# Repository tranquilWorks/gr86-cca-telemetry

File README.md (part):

# CCA Telemetry (GR86 / BRZ Gen2)

## GR86 CCA assurance

The findings-only integration and local Codex prompts are in
[assurance/README.md](assurance/README.md). It binds the current I32 sourced
Rev B package to the shared framework. Fresh native assessment is blocked by
the KiCad 9/10 compatibility gap; software checks do not approve the board.
See [source effectivity](assurance/DISCOVERY.md) before using older descriptions below.

**Current Rev B ECAD and manufacturing:** [sourced I32 handoff](docs/engineering/rvb22/product/PRODUCT_HANDOFF.md).
The native project, BOM, CPL and fabrication files are reconciled; supplier sourcing and physical qualification gates remain open.

CCA Telemetry is a RaceChrono-compatible telemetry stack for the Toyota GR86 / Subaru BRZ (ZN8/ZD8) platform. An ESP32-S3 collects CAN, GPS, and auxiliary analog data, then streams it over Bluetooth Low Energy using RaceChrono's DIY device profile. The codebase is designed for track reliability: aggressive BLE reconnects, TWAI burst handling, persistent configuration, and configurable CAN filtering are all built in.

Hardware bring-up (CAN transceiver wiring, GPS, OLEDs, etc.) is intentionally out of scope here—assume those pieces are already handled. This repository focuses on the firmware, documentation, and validation artifacts you need to build, modify, and deploy the project.

## What this guide covers

* **End-to-end bring-up.** The “Track-day bring-up checklist” walks from flashing through wiring, BLE pairing, and pre-session validation so even a first-time CAN user can connect, configure, and verify the module before heading out.【F:README.md†L46-L125】
* **Subsystem deep dives.** “Firmware architecture,” “Oil pressure channel & calibration,” and the PID-map sections explain how each feature works (CAN ingest, BLE, GPS/PPS, oil analog path, pidmaps) and point directly to the source files for further hacking.【F:README.md†L77-L150】【F:README.md†L206-L213】
* **Runtime operations.** The Serial CLI reference documents every SHOW/PROFILE/ALLOW/FIL/TOKEN/RATE/SAVE command so you can administer the device without reflashing once it is installed in the car.【F:README.md†L214-L244】
* **RaceChrono & filtering workflows.** The RaceChrono integration, `.fil` ingestion walkthrough, and pidmap cloning guide teach you how to curate channels from the phone or at compile time, keeping CAN/BLE bandwidth under control.【F:README.md†L131-L150】【F:README.md†L180-L213】
* **Diagnostics & recovery.** LED pin/pattern tables, the troubleshooting checklist, and persistent-configuration guidance translate firmware counters into hands-on fixes at the car so you can recover from CAN, BLE, GPS, or oil faults mid-event.【F:README.md†L114-L130】【F:README.md†L123-L178】【F:README.md†L238-L244】

Together these sections document the full software feature set—from CAN filtering to RaceChrono streaming and oil calibration—so newcomers can treat the README as a production-ready operations guide.

## Release-ready polish

To make the repo publishable as an open-source reference design, every workflow called out in prior PRs is now paired with actionable guidance in this README:

* **Single source of truth.** The Track-day checklist, subsystem deep dives, CLI catalog, and RaceChrono workflows are all anchored to the implementation files they describe, so readers can jump from prose to code while auditing the feature set.
* **Operator focus.** Each runtime touch point—PID governance, GPS/PPS, oil calibration, RaceChrono filters, persistence—includes both “how it works” and “how to recover” instructions so someone new to CAN can confidently run the module at the track.
* **Debug-to-code breadcrumbs.** LED tables, SHOW/CAL output, and `.fil` logging now cite the handlers that emit those diagnostics, letting contributors trace symptoms back to the firmware without guesswork.

This section is the final assurance that the README stands alone as a production-ready operations manual: new users get the high-level tour at the top, the detailed workflows in the middle, and the debug/persistence references at the end without needing outside docs.

## Feature matrix & documentation coverage

| Feature / decision | Where it lives in code | Where to configure / operate it |
|--------------------|------------------------|----------------------------------|
| CAN burst ingestion, TWAI error recovery, PID throttling | `firmware/cca_telemetry.ino` main loop + TWAI handlers | *Firmware architecture → CAN ingestion & PID governance* and *Track-day bring-up checklist* describe how to wire and validate the bus before driving.【F:firmware/cca_telemetry.ino†L205-L235】【F:README.md†L23-L71】 |
| BLE transport, RaceChrono DIY profile, diagnostics notify | NimBLE setup in `firmware/cca_telemetry.ino` | *Track-day bring-up checklist → Pair with RaceChrono*, *RaceChrono integration*, and the troubleshooting bullets tie the LEDs, CLI, and `.fil` workflow together for new users.【F:firmware/cca_telemetry.ino†L89-L146】【F:README.md†L40-L73】【F:README.md†L120-L152】 |
| GPS + PPS time discipline | `firmware/src/gps_nmea.*`, PPS ISR in the sketch | *Firmware architecture → GPS & PPS discipline* plus the LED/troubleshooting tables walk through wiring, lock states, and debugging steps.【F:firmware/src/gps_nmea.cpp†L1-L210】【F:README.md†L75-L152】 |
| Oil pressure sampling, filtering, calibration, and CAN 0x710 publisher | Analog path in `firmware/cca_telemetry.ino` + `nvs_cfg.*` | *Track-day bring-up checklist*, *Oil pressure channel & calibration*, and the CLI section spell out how to hook up sensors, capture endpoints, and stream the data.【F:firmware/cca_telemetry.ino†L755-L807】【F:README.md†L33-L58】【F:README.md†L190-L225】 |
| PID maps, whitelist/deny list, divider overrides, `.fil` ingestion | `firmware/pidmaps/*.h`, filter characteristic handlers | *Creating your own PID map* and *Allowing extra PIDs from RaceChrono filter files* provide both build-time and runtime workflows, while CLI commands (`PROFILE`, `ALLOW`, `DENY`, `FIL VERBOSE`, `TOKEN`) are cataloged in the Serial CLI reference.【F:firmware/pidmaps/gr86_2022.h†L1-L162】【F:firmware/cca_telemetry.ino†L1360-L1465】【F:README.md†L152-L210】 |
| Persistent configuration and recovery | `firmware/src/nvs_cfg.*` | *Configuration workflow* and *Serial CLI → Persistence & recovery* explain how to edit defaults, capture runtime tweaks, and reset misconfigurations without reflashing.【F:firmware/src/nvs_cfg.cpp†L1-L116】【F:README.md†L171-L199】 |
| LED pinout, blink dictionary, scheduler hooks | `firmware/src/led_status.*`, `firmware/src/sched.hpp` | *Status LED + scheduler* table plus the troubleshooting checklist let a first-time CAN user translate physical indicators into next steps at the car.【F:firmware/src/led_status.cpp†L11-L192】【F:README.md†L92-L152】 |
| Build & flash repeatability | Arduino CLI/IDE instructions in this repo | *Building and flashing* covers both GUI and headless flows; the *Maintenance checklist* calls out regression tests to keep the repo production-ready.【F:README.md†L210-L266】 |

This matrix ensures every subsystem that ships in the firmware is paired with an operator-facing doc section, so a new builder can move from flashing through troubleshooting without chasing external resources.

## Repository layout

```
.
├── README.md                ← You're here
├── docs/                    ← RaceChrono presets and user-facing docs
├── firmware/
│   ├── cca_telemetry.ino    ← Main Arduino sketch for the ESP32-S3
│   ├── config.h             ← User-editable build-time configuration
│   ├── pidmaps/             ← CAN whitelist & scaling definitions
│   └── src/                 ← Reusable C++ helpers (GPS parser, NVS config, LEDs, scheduler)
├── libraries/               ← Vendored Arduino dependencies
```

## Track-day bring-up checklist

These steps walk a first-time CAN user from a blank ESP32-S3 dev module to a working RaceChrono feed. Each item links back to the source so you know which files implement the behavior you are validating.

### 1. Flash and configure the firmware

1. Install the ESP32 support package inside the Arduino IDE or CLI and select the **ESP32S3 Dev Module** target, matching the board the sketch was written for.【F:firmware/cca_telemetry.ino†L1-L20】
2. Open `firmware/config.h` and set the user-facing knobs—`DEVICE_NAME`, `DEFAULT_UPDATE_RATE_DIVIDER`, PPS input (`GPS_PPS_GPIO`), CAN baud, and `ACTIVE_PID_MAP`. These constants gate BLE discovery, the CAN throttle default, and whether PPS disciplining is enabled at boot.【F:firmware/config.h†L4-L27】
3. Build and flash `firmware/cca_telemetry.ino` using the instructions later in this README. The sketch pulls in the vendored libraries automatically, so no additional dependency fetch is required beyond what lives in `libraries/`.【F:firmware/cca_telemetry.ino†L21-L57】
4. Connect to the USB serial console at 115200 8N1, hit enter to reveal the prompt, then run `SHOW CFG` to confirm the compiled defaults (BLE name, profile mode, dividers) match what you edited before heading to the car.【F:firmware/cca_telemetry.ino†L2370-L2395】【F:firmware/cca_telemetry.ino†L3400-L3409】

### 2. Wire and power the module

1. Tie the SN65HVD230 (or equivalent) transceiver’s TXD/RXD pins to `GPIO5`/`GPIO4`, then hook its CANH/CANL pins into the car’s 500 kbps high-speed bus; the firmware leaves the TWAI controller in listen mode until it sees valid frames so you can verify the connection on the bench first.【F:firmware/cca_telemetry.ino†L76-L82】【F:firmware/config.h†L20-L21】
2. Wire your GPS puck to UART1 (`GPIO18` ← GPS TX, `GPIO17` → GPS RX) and land an optional PPS input on `GPIO16` if you want nanosecond-level lap timing—the PPS ISR and slew limiter are already enabled as soon as `GPS_PPS_GPIO` is ≥ 0.【F:firmware/cca_telemetry.ino†L80-L109】【F:firmware/config.h†L11-L15】
3. Route the analog oil-pressure sender into `GPIO1/ADC1_CH0`. The firmware samples, filters, and publishes it on virtual CAN ID `0x710`, so all you need to do trackside is capture two calibration points with the CLI after plumbing the sensor.【F:firmware/cca_telemetry.ino†L5-L7】【F:firmware/cca_telemetry.ino†L755-L775】
4. Land the status LEDs on the default pins (`GPIO46`, `GPIO6`, `GPIO7`, `GPIO8`, `GPIO10`, and `GPIO3`) or adjust the macros in `firmware/src/led_status.h` if your harness is different. The table later in this README explains every blink pattern you will see once the car powers the unit.【F:firmware/src/led_status.h†L6-L32】【F:firmware/cca_telemetry.ino†L1368-L1373】

### 3. Pair with RaceChrono and feed channels

1. Power the car or bench supply so the ESP32 starts advertising under the `DEVICE_NAME` you configured. RaceChrono will discover the DIY service (`0x1FF8`) plus the CAN, GPS, GPS-time, filter, and diagnostics characteristics defined in the sketch.【F:firmware/cca_telemetry.ino†L89-L95】
2. Import `docs/racechrono_preset.md` into RaceChrono to create ready-made channels for every GR86/BRZ PID in the curated allow-list, including the synthetic oil frame on `0x710`. This saves you from typing scaling equations on the phone.【F:docs/racechrono_preset.md†L1-L68】
3. If you need to add or remove CAN IDs directly from your phone, issue a `TOKEN <hex8>` over serial and then push a `.fil` file from RaceChrono’s *Manage filters* UI. Each command in the file becomes an ALLOW/DENY write on characteristic `0x0002`, which the firmware authenticates with the token before applying it to the runtime map.【F:firmware/cca_telemetry.ino†L1360-L1465】【F:firmware/cca_telemetry.ino†L3613-L3647】
4. Finish the pairing pass by checking `SHOW MAP` / `SHOW DENY` and the BLE diagnostics characteristic (`0x0005`) so you know the RaceChrono UI and the firmware are in sync before the session.【F:firmware/cca_telemetry.ino†L3345-L3505】【F:firmware/cca_telemetry.ino†L867-L920】

### 4. Validate data flow and hit the track

1. Watch the LED bank: solid power LED plus pulsing CAN/GPS LEDs indicate the car is broadcasting and GPS sentences are flowing, while the SYS LED warns about BLE throttling so you can bump dividers before packets drop.【F:firmware/src/led_status.h†L6-L32】【F:firmware/cca_telemetry.ino†L3732-L3879】
2. Use `SHOW STATS` after a shakedown lap to confirm there are no CAN timeouts, TWAI restarts, or BLE notify drops. The counters cover every subsystem mentioned earlier in this README.【F:firmware/cca_telemetry.ino†L3411-L3438】
3. Run `CAL SHOW`, `SHOW CFG`, and `RATE` to double-check that oil calibration, broadcast cadence, and profile mode match what you expect before logging laps; save any runtime tweaks so they persist across pit cycles.【F:firmware/cca_telemetry.ino†L3507-L3575】【F:firmware/cca_telemetry.ino†L3566-L3575】【F:firmware/cca_telemetry.ino†L782-L807】

## Firmware architecture

The sketch in `firmware/cca_telemetry.ino` orchestrates several subsystems:

* **CAN ingestion** – `ESP32-TWAI-CAN` runs the ESP32's native TWAI controller in RX burst mode. PID throttling keeps BLE bandwidth under control while the `pidmaps` whitelist ensures only RaceChrono-ready signals are forwarded.
* **BLE transport** – `NimBLE-Arduino` implements the RaceChrono DIY profile (service `0x1FF8`). Notifications are rate-limited with an adaptive governor, reconnection restarts advertisers instead of destroying the controller, and diagnostic counters identify congestion/backpressure.
* **GPS & PPS discipline** – `firmware/src/gps_nmea.*` parses RMC/GGA sentences and disciplines system time to an external PPS input with slew limiting.
* **Persistent configuration** – `firmware/src/nvs_cfg.*` stores calibration data (analog dividers, device profile, etc.) in NVS so tweaks survive power cycles.
* **Status LED + scheduler** – `firmware/src/led_status.*` and `firmware/src/sched.hpp` provide non-blocking indicators and lightweight cooperative task scheduling for housekeeping loops.
* **RaceChrono mapping** – `firmware/pidmaps/` encapsulates CAN scaling/units per signal. `config.h` selects the active table and exposes knobs such as BLE device name, update dividers, and analog calibration constants.

### Subsystem deep dive

#### CAN ingestion and PID governance

The CAN stack configures TWAI alerts for RX queue overruns, bus-off, arbitration loss, and other critical faults, then polls those counters each second to decide when to restart the controller or surface diagnostic frames back to RaceChrono.【F:firmware/cca_telemetry.ino†L205-L235】 Above that, the `pidmaps` layer predefines the GR86/BRZ whitelist plus default per-ID dividers and lets the CLI flip between strict allow-list streaming (`PROFILE ON`) or a sniff-all fall-through that still honors the runtime deny list.【F:firmware/pidmaps/gr86_2022.h†L9-L118】【F:firmware/cca_telemetry.ino†L718-L865】 Custom divider overrides are persisted and applied on boot so you can bump individual CAN IDs without recompiling, and the same bookkeeping powers `SHOW MAP`, `ALLOW`, and `DENY` in the serial console.【F:firmware/cca_telemetry.ino†L712-L865】【F:firmware/cca_telemetry.ino†L3345-L3505】

**Whitelist, blacklist, and dividers.** Each entry in `firmware/pidmaps/*.h` carries a target RaceChrono channel plus a default divider, meaning “forward one in every _N_ frames for this CAN ID.” Lower dividers increase BLE load; higher ones conserve bandwidth for low-value or high-frequency signals. `PROFILE ON` enforces this whitelist (only IDs present in the map are forwarded) while `PROFILE OFF` switches to “sniff everything” and relies on the deny list to suppress noisy IDs. `ALLOW <pid> <div>` temporarily whitelists additional IDs with their own dividers, whereas `DENY <pid>` forces the firmware to drop that ID even if the profile is off or the ID appears in the static map. Both overrides are stored in NVS via `SAVE` so trackside experiments persist across reboots.【F:firmware/cca_telemetry.ino†L3341-L3609】

#### BLE transport and congestion control

`NimBLE-Arduino` exposes the full DIY profile (CAN, filter, GPS, GPS time, and diagnostics characteristics) and negotiates aggressive 7.5–15 ms connection intervals to keep RaceChrono synced.【F:firmware/cca_telemetry.ino†L275-L357】 A moving-average notify governor tracks bytes-per-second, clamps burst size, and progressively backs off when congestion or ATT errors show up, with event counters logged through `SHOW STATS` and the diagnostics characteristic so you know whether BLE or CAN is the bottleneck.【F:firmware/cca_telemetry.ino†L139-L174】【F:firmware/cca_telemetry.ino†L867-L920】 The reconnection path restarts advertisers and reapplies MTU sizing automatically, so unplugging power or losing the phone link no longer wedges the NimBLE host.【F:firmware/cca_telemetry.ino†L301-L357】

#### GPS and PPS discipline

`gps_nmea.cpp` parses both RMC and GGA sentences, clamps checksum errors, and normalizes latitude/longitude/altitude fields, while the main sketch tracks the GPS init state machine (autobaud probing, fallback timers, and periodic notify cadence).【F:firmware/src/gps_nmea.cpp†L1-L121】【F:firmware/src/gps_nmea.cpp†L123-L198】【F:firmware/cca_telemetry.ino†L237-L274】 When a PPS input is wired, the ISR debounces the pulse, estimates drift, and slews the system clock by ±2 ms/second to keep RaceChrono’s GPS and CAN timestamps aligned, which dramatically reduces lap interpolation error.【F:firmware/cca_telemetry.ino†L176-L188】

#### Persistent configuration and CLI tie-in

The `nvs_cfg` helpers serialize oil calibration voltages, versioning, and CRCs into the `cca_cfg` namespace so even power-cycled cars retain the analog slope you captured with `CAL` commands.【F:firmware/src/nvs_cfg.cpp†L1-L75】 Raw blobs can be inspected with `CAL SHOW`, and the same module exposes guard rails (finite, monotonic voltages) to keep corrupt data from applying at boot.【F:firmware/src/nvs_cfg.cpp†L76-L116】 In addition to analog endpoints, NVS stores PID divider overrides, custom oil broadcast rates, FIL tokens, and the profile bit so the CLI “SAVE / LOAD / RESETCFG” workflow mirrors what’s burned into flash.【F:firmware/cca_telemetry.ino†L782-L865】【F:firmware/cca_telemetry.ino†L3650-L3674】

#### Status LED + scheduler

`led_status.*` defines six independent channels (power, BLE, CAN, GPS, SYS, oil) with per-pin polarity, a library of blink/pulse patterns, and a tiny state machine that updates the GPIOs without blocking other tasks.【F:firmware/src/led_status.cpp†L11-L192】 Time-sliced housekeeping loops use the `every()` helper in `sched.hpp` to run at deterministic cadences (GPS notify, CAN diagnostics, oil broadcasts) even when other work momentarily stalls the main loop.【F:firmware/src/sched.hpp†L5-L23】

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
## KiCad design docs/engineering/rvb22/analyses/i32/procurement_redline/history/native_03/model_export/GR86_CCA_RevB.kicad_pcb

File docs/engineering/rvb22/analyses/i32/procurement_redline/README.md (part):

# I32 procurement redline — completed desktop verification

The frozen procurement set is applied to the actual native candidate, with regenerated assembly/fabrication outputs. All 14 requested desktop gate categories pass within the declared model and supplier-catalogue scope. This is not an order authorization, supplier acceptance, hardware validation or full-product qualification.

The starting remote revision was `1c934f9ddd7a1b823e5136484f525485472528f6` on `codex/rvb24-coordinated-closure`, PR #46. The immutable pre-redline CAD commit is `e5ef8425dbe59c99e99eabb75c04342a47b27561`. Its four subsequent evidence/handoff commits remain ancestors. The final publication commit is the commit containing this report; the PR publication record identifies the remote SHA without a self-referential file hash.

Current authority is [FINAL_REDLINE_VERIFICATION.json](FINAL_REDLINE_VERIFICATION.json), [SOURCE_BINDING.json](SOURCE_BINDING.json), and [the manufacturing manifest](../../../current/i32_manufacturing/SOURCE_MANIFEST.json). [CHANGED_PATHS.md](CHANGED_PATHS.md) enumerates every changed CAD, model, manufacturing and evidence path. Original current records are preserved under `history/pre_redline/`; existing experiment history and the controlling readiness/handoff documents remain intact.

| Native artifact | SHA256 |
|---|---|
| Authored PCB | `52ca35cf8cb4e2b4a27d053686ee3a85564f1e94dfdb7dcb4bca4083dd527312` |
| KiCad filled PCB | `896ca56bf4ad836d63b84537cfd20bfcbf1783c60ac5d92ab7c7783d54f57e92` |
| Native schematic XML | `3a3ac0ad2e7acc75bd5690a128a7d47e28859e017c66fe01276025dfa7dda93d` |

## Exact substitutions

| References | Frozen MPN | JLC/LCSC | Package |
|---|---|---|---|
| C152,C154,C165 | CGA3E3X7R1H224KT0Y0N | C342967 | 0603 |
| L121 | BPCI00121280470M00 | C6471075 | 12 × 12 mm SMD |
| R155 | PTFR0603B11K8N9 | C19679768 | 0603 |
| R156 | PLT1206Z5051LBTS | C4074185 | **1206** |
| R160 | RT0805BRB076K34L | C864499 | **0805** |
| R161,R163,R170 | PTFR0603Q1K00N9 | C23067434 | 0603 |
| R162 | PTFR0603Q4K70N9 | C23067437 | 0603 |
| R169 | PTFR0603B3K01N9 | C2692830 | 0603 |
| U101 | LTC4367HMS8#PBF | C688370 | MSOP-8 |

U101 remains the H-grade electrical device. The owner accepts losing the **#W controlled-manufacturing ordering pedigree**. The #PBF pedigree is not equivalent. This acceptance is recorded in the native schematic and PCB properties. F101 and U401 remain unchanged local/manual installations. No unrelated MPN was substituted. R151's previously missing PCB LCSC field was reconciled to the already-existing schematic/BOM value C190124; all its electrical and physical properties are unchanged.

## Physical and model changes

All 13 frozen references use checked `RevB:I32_PROCUREMENT_<ref>` footprints. Manufacturer documents, exact file hashes, pad/net checks, body dimensions, mask/paste membership and model distinctions are in [PACKAGE_QUALIFICATION.json](PACKAGE_QUALIFICATION.json). Nine new STEP files are dimensionally correct generic maximum-body envelopes, explicitly not vendor CAD. Existing capacitor and MSOP generic models remain, with maximum body/tolerance covered in the mechanical check. All 177 fitted models resolve in the populated STEP export.

| Ref | Native placement (mm, degrees) | Physical change |
|---|---|---|
| R156 | B.Cu, (41.25, 10.101), −90° | 0603 → 1206. Vishay 60119 lands: 0.9144 × 1.7018 mm at ±1.524 mm. Maximum body 3.4032 × 1.7272 × 0.8382 mm; courtyard 4.5 × 2.25 mm. Ground-pad centre retained at (41.25, 11.625). Added 0.25 mm feedback copper to the moved pad. |
| R160 | F.Cu, (27.0, −7.5), 0° | 0603 → 0805. Lands 1.0 × 1.45 mm at ±1.025 mm; maximum body 2.1 × 1.35 × 0.6 mm. Courtyard 3.55 × 1.95 mm. Centre/orientation unchanged. |
| L121 | F.Cu, (59.8, 29.05), 90° | Replaced Coilcraft-specific pattern with the BPCI manufacturer pattern: 5.4 × 2.8 mm pads, 7 mm inner gap, 9.8 mm centre spacing, 12.6 mm outer span. Maximum body 12.5 × 12.5 × 8 mm; 13.1 mm courtyard. Moved −0.2/+0.05 mm to preserve nearby protected clearances. |
| R155 | B.Cu, (44.0, 10.8), 90° | Qualified PTFR lands; shifted −0.55 mm in X for package spacing. |
| R169 | B.Cu, (79.8, 1.7), 0° | Qualified PTFR lands; shifted −0.2/−0.3 mm. |
| R170 | B.Cu, (83.2, 1.7), 0° | Qualified PTFR lands; shifted −0.1/−0.3 mm. |

R161/R162/R163 also receive the actual PTFR pattern: 0.9 × 1.2 mm pads at ±0.95 mm, within the manufacturer's dimensional land-pattern range. The same-package capacitor and U101 substitutions preserve pad sizes and pin/net identity. Pads, paste, mask, courtyards, copper/via clearances and native orientation are checked for all changed references.

Routing moves the 3V3_ENABLE left leg to X25.1 and crossbar to Y−8.6; the 3V3_VIN sense crossbar to Y−5.0; and the 5V_RIPPLE leg to X53.1375. The LED_OIL ordinary 0.6/0.3 mm via moves from (41.1, 8.3) to (38.3, 8.9), with its B.Cu and In2.Cu connections rerouted. These changes clear enlarged pads while preserving all pad nets. The source audit records one added segment, 18 modified copper objects, no removed copper objects and no added or removed vias. All 49 special vias, stackup, custom clearances and rules remain unchanged. The complete UUID-level delta is in [SOURCE_AUDIT.json](SOURCE_AUDIT.json); annotated route views are in `layout/`.

## Verification and manufacturing

| Gate | Result and retained evidence |
|---|---|
| Native KiCad 9.0.9 | ERC 0, DRC 0, unconnected 0, schematic/PCB parity 0, exclusions 0; 13/13 output postconditions. `native_final/` |
| Exact source | 157 CAD files bound; 32 firmware files unchanged. Original GPIO, receive-only CAN, RF, GPS and oil signal contracts retained. `SOURCE_AUDIT.json` |
| Independent copper/export reconstruction | PASS across 145 nets and 571 net-bearing pads, with no disconnected pad nets or pad/net mismatches; Gerber flashes/traces/fills and drill exports matched. `manufacturing_audit_final/` |
| Explicit source copper | Zero new/worsened foreign-net gaps below 0.15 mm, zero prior pad-connectivity regressions and no unsupported primitives. `EXPLICIT_COPPER_FINAL.json` plus exact metadata rebind |
| Power returns | 23/23 actual-filled ground pairs connected. Source return 11.282 mΩ against 15 mΩ; C206 allocation 10.919 mΩ against 11 mΩ. `filled_returns_final/`, `ground_final/` |
| Packages/models | 13/13 exact identities, pad nets, lands, models and mask/paste memberships checked. `PACKAGE_QUALIFICATION.json` |
| BOM/CPL | 177 fitted; 175 factory CPL rows; F101/U401 local; C203/R301/R306 DNP. Every frozen ref has its exact MPN/C-number; zero old frozen MPNs in active BOM. `MANUFACTURING_RECONCILIATION.json` |
| Manufacturing | 11 Gerber layers, 2 drill files, 1 job file; IPC-D-356, schematic PDF/XML, populated STEP, 49-via list and editable CAD copy regenerated. `current/i32_manufacturing/` |
| Mechanical | 1,308 populated checks, 529 mated checks, 38 probe approaches; no modeled interference. Full 1.71 mm height stack; minimum allocated clearance 0.120 mm. `mechanics_final/` |
| Analysis binding | 16 existing native-binding unit tests passed. Full filled-tree comparison preserves every physical/model token and native filled polygon across the final descriptive cleanup. `NATIVE_BINDING_TESTS.log`, `METADATA_ONLY_REBIND.json` |

Native CPL coordinates use the retained auxiliary origin (0, 41.288863) mm. R156: Bottom, X41.25/Y31.187863, −90°; R160: Top, X27/Y48.788863, 0°; L121: Top, X59.8/Y12.238863, 90°. All 175 rows reconcile against native reference, side, X/Y and rotation. Supplier feeder/pin-one and bottom-side interpretation remain assembly setup acceptance items.

The factory list contains **29 unchanged references without assigned LCSC codes**, enumerated in `assembly/SOURCING_REQUIRED.csv`. This redline resolves the frozen set; it does not authorize opportunistic substitutions or claim that the entire BOM is turnkey-order-ready.

## Fresh electrical replay

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
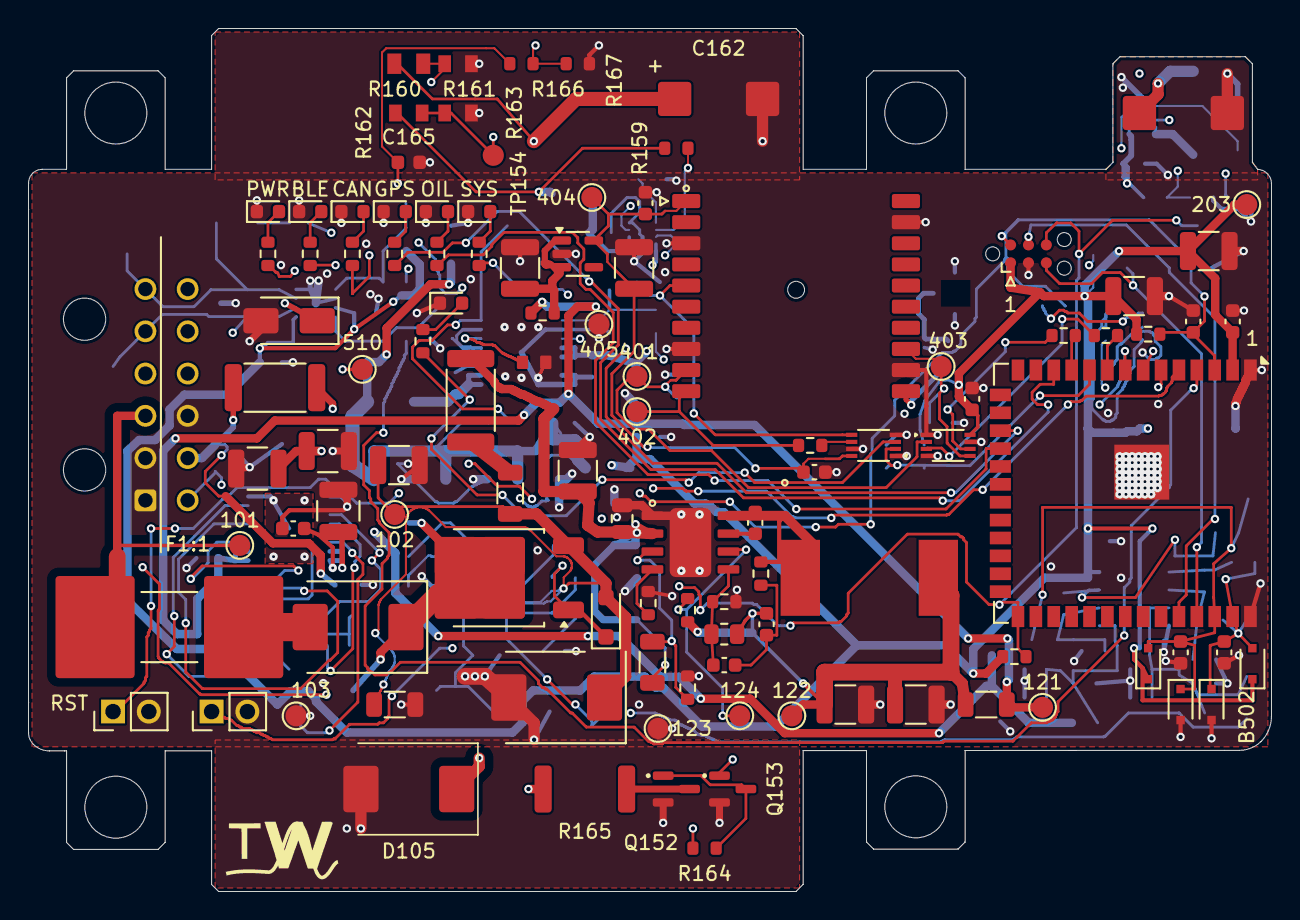
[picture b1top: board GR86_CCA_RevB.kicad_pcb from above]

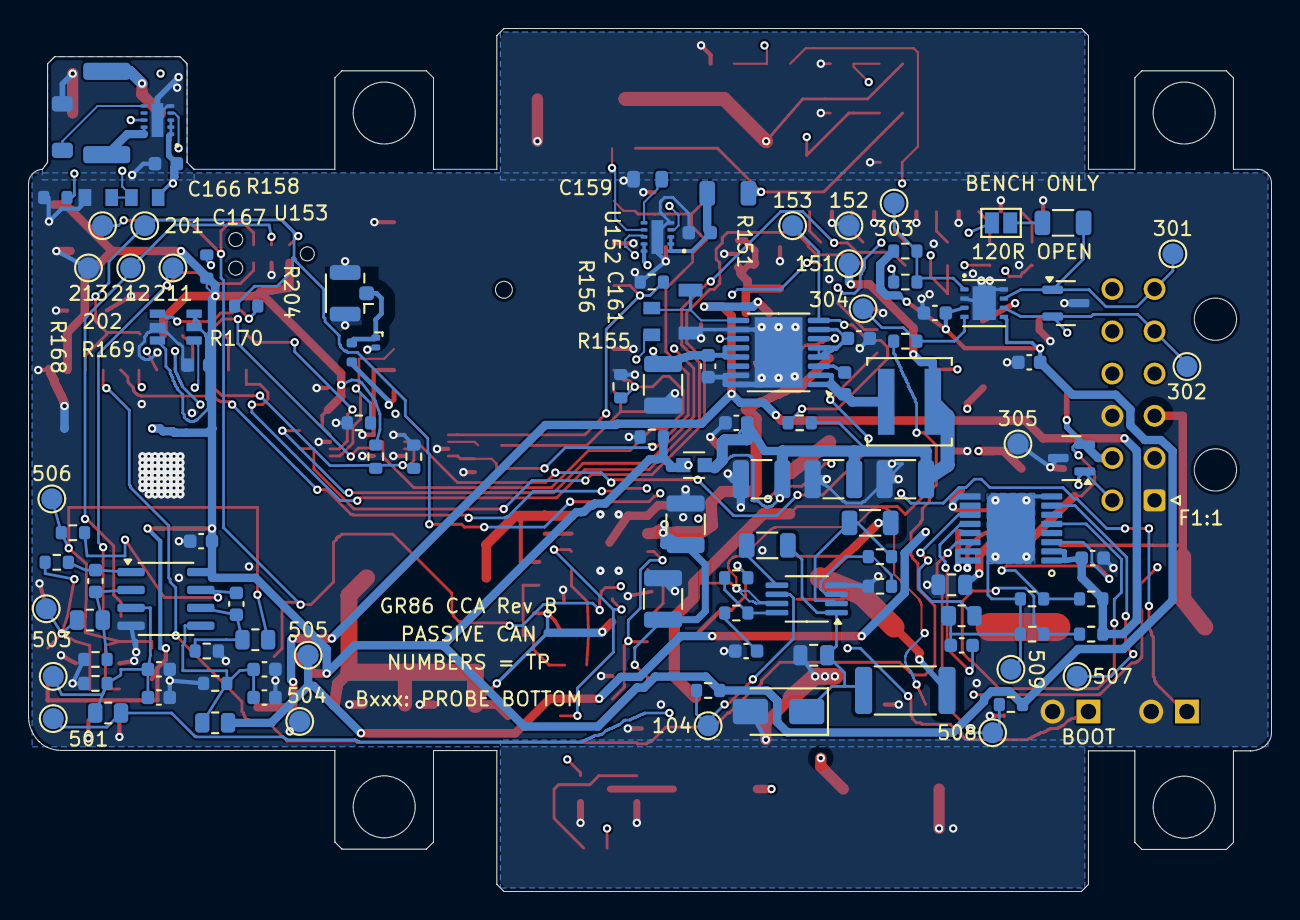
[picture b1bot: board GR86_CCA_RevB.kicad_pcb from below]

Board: 4 copper layers, 88.3 x 61.3 mm, 224 parts (113 on the bottom side), 104 nets.

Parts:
C101, C123, C503: 100n /100V X7R; C_0805_2012Metric
C102: 10n /100V X7R; C_0603_1608Metric
C103, C121, C122, C129: 2.2u /100V X7R; C_1210_3225Metric
C124: 2.2n /50V C0G 5%; C_0603_1608Metric
C125: 3.3n /100V C0G 5%; C_0603_1608Metric
C126: 100p /50V C0G; C_0603_1608Metric
C127, C128, C151, C155, C156, C157, C201, C204, C401, C402: 22u /25V X7R 10%; C_1210_3225Metric
C152: 220n /50V X7R 10%; I32_PROCUREMENT_C152
C153, C302, C511, C512, C521, C522: 1u /16V X7R; C_0603_1608Metric
C154: 220n /50V X7R 10%; I32_PROCUREMENT_C154
C158, C202, C301, C403, C404, C405, C502, C531: 100n /50V X7R; C_0603_1608Metric
C159: 33n /100V C0G 5% CT; I32_FINISHED_C159
C161: 100n /50V X7R ISO INPUT; I32_FINISHED_C161
C162: 470u /10V POLYMER INPUT; I32_FINISHED_C162
C165: 220n /50V X7R 10% EN DELAY; I32_PROCUREMENT_C165
C166: 68n /100V C0G 5% BULK CT; I32_FINISHED_C166
C167: 1u /16V X7R BULK INPUT; I32_FINISHED_C167
C203: 1u DNP - SUPERVISOR ECO; C_0603_1608Metric
C205: 100n /50V X7R; C_0603_1608Metric_RVB22_C205
C206: 680u /6.3V POLYMER; KEMET_T598_X_7343_Median_RVB22_C206
C501, C513, C523: 22n /50V X7R; C_0603_1608Metric
C504, C505, C506: 10u /50V X7R; KEMET_C1210_10u50V
C514, C524: 100p /50V C0G5%; C_0603_1608Metric
C532: 10n /50V C0G 5% OUT HF; C_0603_1608Metric
D101: S5J /600V REVERSE BLOCK; D_SMC
D102: SMAJ30A /TVS; D_SMA
D103: SMCJ24A /TVS; D_SMC_RVB22_D103
D104: 15V GATE CLAMP; D_SOD-123F
D105: SMCJ110A /RAW OV CLAMP; D_SMC
D301, D501: ESD2CAN24DBZRQ1; SOT-23
D401: SEARCH (blink / no fix); LED_0603_1608Metric
D402: TPD1E05U06DPYR; TI_DPY0002A_TPD1E05U06_SMDMask
D502: SS16 /60V Schottky; D_SMA
D511, D512, D521, D522: PMEG2010BEA,115; Nexperia_SOD323_PMEG2010BEA
D601: PWR; LED_0603_1608Metric
D602: BLE; LED_0603_1608Metric
D603: CAN; LED_0603_1608Metric
D604: GPS; LED_0603_1608Metric
D605: SYS; LED_0603_1608Metric
D606: OIL; LED_0603_1608Metric
F1: 0430451200 / TIN NEW HARNESS; Molex_Micro-Fit_3.0_43045-1200_2x06_P3.00mm_Horizontal_RVB2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
F101: 1A /500VDC; Fuse_Littelfuse-NANO2-885
J201: TC2030-IDC-NL / UART; Tag-Connect_TC2030-IDC-NL_2x03_P1.27mm_Vertical
J202: RESET — short to reset; Wurth_61300211121_1x02
J203: BOOT — hold low on reset; Wurth_61300211121_1x02
J401: U.FL-R-SMT-1(80); Hirose_UFL_R_SMT_1_80_RevB
L121: 47u /100mOhm 2.5A BPCI; I32_PROCUREMENT_L121
L151: 15u /XGL5030; L_Coilcraft_XAL5030-XXX
L406: 1.6nH 5% RF MATCH; Murata_LQW18AS_1608
MH901, MH902, MH903, MH904: 4.4mm NPTH; MountingHole_4.4mm_Outboard
Q101: STD25NF20 /200V; TO-252-2
Q152: DMG2302UKQ /DISCHARGE; I32_FINISHED_Q152
Q153: DMG2302UKQ /DISCHARGE; I32_FINISHED_Q153
R101: 12.1k /1W CTRL SURGE FEED; R_2512_6332Metric
R102: 549k /0.1% OV COORD; R_1206_3216Metric
R103: 24.3k /0.1% UV OV COORD; R_0603_1608Metric
R104: 14.7k /0.1%; R_0603_1608Metric
R105: 510k; R_1206_3216Metric
R106: 10R /gate; R_0603_1608Metric
R107: 5.1k /slew branch; R_0603_1608Metric
R108, R127, R152, R407, R408, R409, R506: 100k; R_0603_1608Metric
R109: 0R INPUT ISOLATION; R_1206_3216Metric
R110: 0.47R /0.815W filter; R_2512_6332Metric
R111: 100k /bleed; R_1206_3216Metric
R121: 31.6k /RON; R_0603_1608Metric
R122: 309k /0.1%; R_0805_2012Metric
R123: 100k /0.1%; R_0603_1608Metric
R124: 43.2k /RA; R_0603_1608Metric
R125: 100k; R_1206_3216Metric
R126: 26.1k; R_0603_1608Metric
R128: 0R 5V ISOLATION; R_1206_3216Metric
R151: 0R MAIN INPUT ISOLATION; I32_FINISHED_R151
R153: 10mR MAIN OUTPUT ISOLATION; WSLP0603_MANUFACTURER_R153
R154: 1k /rail bleed; R_0603_1608Metric
R155: 11.8k /0.1% 10ppm FB TOP; I32_PROCUREMENT_R155
R156: 5.05k /0.01% 5ppm FB BOTTOM; I32_PROCUREMENT_R156
R157: 10k /1% VSEL ADJUST; R_0603_1608Metric_RVB22_R157
R158: 300m /1% BULK DAMPING; I32_FINISHED_R158
R159: 47k /1% PG PULLUP; I32_FINISHED_R159
R160: 6.34k /0.1% 10ppm SNS TOP; I32_PROCUREMENT_R160
R161: 1k /0.02% 10ppm SNS BOTTOM; I32_PROCUREMENT_R161
R162: 4.7k /0.02% 10ppm ISO EN TOP; I32_PROCUREMENT_R162
R163: 1k /0.02% 10ppm ISO EN BOTTOM; I32_PROCUREMENT_R163
R164: 4.7k /DISCHARGE GATE FEED; I32_FINISHED_R164
R165: 4.7R /1.5W PULSE DISCHARGE; I32_FINISHED_R165
R166: 330k /1% U151 EN DIVIDER; I32_FINISHED_R166
R167: 330k /1% U151 EN DIVIDER; I32_FINISHED_R167
R168: 1k /1% RESERVOIR BLEED; I32_FINISHED_R168
R169: 3.01k /0.1% 10ppm BULK EN TOP; I32_PROCUREMENT_R169
R170: 1k /0.02% 10ppm BULK EN BOTTOM; I32_PROCUREMENT_R170
R201, R202, R303: 10k 1%; R_0603_1608Metric
R203: 1k 1% RESET LIMIT; R_0603_1608Metric_RVB22_R203
R204: 100k /1% RESET DELAY; I32_FINISHED_R204
R301: 0R DNP; R_0603_1608Metric
R302, R405: 1k; R_0603_1608Metric
R306: 120R 1% DNP; R_1206_3216Metric
R401: 0R GPS ISOLATION; R_0603_1608Metric
R402, R403, R404: 220R; R_0603_1608Metric
R410: 10k /UART idle; R_0603_1608Metric
R411: 100k /off-state; R_0603_1608Metric
R501: 27.4k /0.1%; R_0603_1608Metric
R502, R504: 10k /0.1%; R_0603_1608Metric
R503: 36.5k /0.1%; R_0603_1608Metric
R505: 118k /0.1%; R_0805_2012Metric
R507: 4.7R /1% pulse HP; R_2512_6332Metric
R511, R521: 1M /0.1%; R_0805_2012Metric
R512, R522: 4.02k /0.1%; R_0603_1608Metric
R513, R523: 124k /0.1%; R_0805_2012Metric
R514, R524: 1k /0.1%; R_0603_1608Metric
R515, R525: 220R /1%150ppm; R_0603_1608Metric
R601: 1k / GPIO15; R_0603_1608Metric
R602: 1k / GPIO6; R_0603_1608Metric
R603: 1k / GPIO7; R_0603_1608Metric
R604: 1k / GPIO8; R_0603_1608Metric
R605: 1k / GPIO10; R_0603_1608Metric
R606: 1k / GPIO9; R_0603_1608Metric
SJ301: BENCH TERM OPEN; SolderJumper-2_P1.3mm_Open_Pad1.0x1.5mm
TP101: TP_RAW_12V; TestPoint_Pad_D1.5mm
TP102: TP_PROTECTED_12V; TestPoint_Pad_D1.5mm
TP103: TP_INPUT_GND; TestPoint_Pad_D1.5mm
TP104: TP_INPUT_FAULT; TestPoint_Pad_D1.5mm
TP121: TP_5V; TestPoint_Pad_D1.5mm
TP122: TP_5V_SOURCE; TestPoint_Pad_D1.5mm
TP123: TP_5V_GND; TestPoint_Pad_D1.5mm
TP124: TP_5V_PGOOD; TestPoint_Pad_D1.5mm
TP151: TP_3V3_SOURCE; TestPoint_Pad_D1.5mm
TP152: TP_MAIN_GND; TestPoint_Pad_D1.5mm
TP153: TP_3V3_PGOOD; TestPoint_Pad_D1.5mm
TP154: TP_ISO_ENABLE; I32_FINISHED_TP154
TP201: TP_EN; TestPoint_Pad_D1.5mm
TP202: TP_GPIO0; TestPoint_Pad_D1.5mm
TP203: TP_3V3; TestPoint_Pad_D1.5mm
TP211: TP_UART0_TX; TestPoint_Pad_D1.5mm
TP212: TP_UART0_RX; TestPoint_Pad_D1.5mm
TP213: TP_DEBUG_GND; TestPoint_Pad_D1.5mm
TP301: TP_CANH; TestPoint_Pad_D1.5mm
TP302: TP_CANL; TestPoint_Pad_D1.5mm
TP303: TP_CAN_TXD; TestPoint_Pad_D1.5mm
TP304: TP_CAN_RXD; TestPoint_Pad_D1.5mm
TP305: TP_CAN_GND; TestPoint_Pad_D1.5mm
TP401: TP_GPS_TX; TestPoint_Pad_D1.5mm
TP402: TP_GPS_RX; TestPoint_Pad_D1.5mm
TP403: TP_GPS_PPS; TestPoint_Pad_D1.5mm
TP404: TP_GPS_3V3; TestPoint_Pad_D1.5mm
TP405: TP_GPS_GND; TestPoint_Pad_D1.5mm
TP501: TP_OIL_SIG; TestPoint_Pad_D1.5mm
TP502: TP_OIL_FILTERED; TestPoint_Pad_D1.5mm
TP503: TP_ADC_NODE; TestPoint_Pad_D1.5mm
TP504: TP_OIL_GND; TestPoint_Pad_D1.5mm
TP505: TP_OIL_5V; TestPoint_Pad_D1.5mm
TP506: TP_OIL_EXC_ADC; TestPoint_Pad_D1.5mm
TP507: TP_OIL_SHDN; TestPoint_Pad_D1.5mm
TP508: TP_OIL_POWER_FAULT; TestPoint_Pad_D1.5mm
TP509: TP_OIL_EFUSE_RTN; TestPoint_Pad_D1.5mm
TP510: TP_OIL_EFUSE_OUT; TestPoint_Pad_D1.5mm
U101: LTC4367HMS8#PBF; I32_PROCUREMENT_U101
U121: LM5164QDDARQ1; TI_DDA0008B_4214849B
U151: LM63615DQPWPRQ1; HTSSOP-16-1EP_4.4x5mm_P0.65mm_EP3.4x5mm_Mask2.46x2.31mm_RVB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
U152: TPS22953-Q1 REVERSE BLOCKING; I32_FINISHED_U152
U153: TPS22953-Q1 BULK CHARGER; I32_FINISHED_U153
U201: ESP32-S3-WROOM-1-N8R2; ESP32-S3-WROOM-1_RVB22_U201_TH48
U202: TPS3808G33-Q1 3.07V RESET; TPS3808_DBV0006A
U301: TCAN3403DRBRQ1; TI_DRB0008J_TCAN3403
U401: PA1616D; CDTop_PA1616D_20Pad_v06
U402, U404: SN74LVC2G125DCUR; VSSOP-8_2.3x2mm_P0.5mm
U403: MIC5504-3.3YM5-TR; SOT-23-5
U501: TPS26600PWPR; TI_PWP0016A_TPS2660
U502: OPA2333AIDR; SOIC-8_3.9x4.9mm_P1.27mm

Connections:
3V3_BOOT: C154.1, U151.3
3V3_BUCK_ENABLE: R166.2, R167.1, U151.11
3V3_BULK_CT: C166.1, U153.6
3V3_BULK_DAMPED: C206.1, R158.2, R168.1
3V3_BULK_ENABLE: R169.2, R170.1, U153.4
3V3_BULK_SWITCHED: R158.1, U153.9, U153.10
3V3_DISCHARGE_DRAIN: Q152.3, R165.2
3V3_DISCHARGE_GATE: Q152.1, Q153.3, R164.2
3V3_ENABLE: C165.1, Q153.1, R159.2, R166.1, U152.7 (PG)
3V3_FB_ADJ: R155.2, R156.1, U151.9
3V3_ISO_CT: C159.1, U152.6 (CT)
3V3_ISO_ENABLE: R162.2, R163.1, TP154.1, U152.4 (EN)
3V3_ISO_IN: C161.1, R151.2, U152.1 (IN1), U152.2 (IN2), U152.3 (BIAS)
3V3_ISO_SNS: R160.2, R161.1, U152.8 (SNS)
3V3_PGOOD: R152.2, TP153.1, U151.8
3V3_SOURCE: C155.1, C156.1, C157.1, C158.1, L151.2, R152.1, R153.1, R155.1, R165.1, TP151.1
3V3_SW: C154.2, L151.1, U151.1, U151.2
3V3_VCC_INTERNAL: C153.1, U151.4, U151.5, U151.7
3V3_VIN: C151.1, C152.1, C162.1, R160.1, R164.1, U151.12, U151.13, U152.9 (OUT1), U152.10 (OUT2)
3V3_VSEL_ADJ: R157.1, U151.6
5V_BST: C124.1, U121.7
5V_EN: R125.2, R126.1, U121.3
5V_FB: C126.2, R122.2, R123.1, U121.5
5V_PGOOD: R127.2, TP124.1, U121.6
5V_RIPPLE: C125.1, C126.1, R124.2
5V_RON: R121.1, U121.4
5V_SOURCE: C125.2, C127.1, C128.1, L121.2, R122.1, R127.1, R128.1, TP122.1
5V_SW: C124.2, L121.1, R124.1, U121.8
5V_VIN: C121.1, C122.1, C123.1, C129.1, R110.2, R125.1, U121.2
+3V3: C167.1, C201.1, C202.1, C204.1, C205.1, C301.1, C302.1, C404.1, C531.1, D511.1, D521.1, J201.1, R108.1, R153.2, R154.1, R169.1, R201.1, R202.1, R204.1, R303.1, R410.1, R506.1, TP203.1, U153.1, U153.2, U153.3, U153.8, U201.2, U202.3, U202.5, U202.6, U301.3, U301.5, U402.8, U502.8
+5V: C502.1, R128.2, R151.1, R159.1, R162.1, R401.1, R501.1, R503.1, TP121.1, U501.1, U501.2
ADC_NODE: C513.1, D511.2, D512.1, R513.1, R515.2, TP503.1, U201.39
BUCK_FEED: R109.2, R110.1
CANH: D301.1, F1.6, R306.1, TP301.1, U301.7
CANL: D301.2, F1.5, SJ301.2, TP302.1, U301.6
CAN_RXD: R302.1, TP304.1, U301.4
CAN_RX_MCU: R302.2, U201.4
CAN_TERM_LINK: R306.2, SJ301.1
CAN_TXD: R301.2, R303.2, TP303.1, U301.1
CAN_TX_MCU: R301.1, U201.5
ESP_EN: C203.1, J201.2, J202.1, R201.2, R203.2, TP201.1, U201.3
ESP_GPIO0: J201.6, J203.1, R202.2, TP202.1, U201.27
FUSED_12V: D101.2, F101.2
GND: C101.2, C102.2, C103.2, C121.2, C122.2, C123.2, C127.2, C128.2, C129.2, C151.2, C152.2, C153.2, C155.2, C156.2, C157.2, C158.2, C159.2, C161.2, C162.2, C165.2, C166.2, C167.2, C201.2, C202.2, C203.2, C204.2, C205.2, C206.2, C301.2, C302.2, C401.2, C402.2, C403.2, C404.2, C405.2, C502.2, C503.2, C504.2, C505.2, C506.2, C511.2, C512.2, C513.2, C521.2, C522.2, C523.2, C531.2, C532.2, D102.2, D103.2, D105.2, D301.3, D401.1, D402.2, D501.3, D502.2, D512.2, D522.2, D601.1, D602.1, D603.1, D604.1, D605.1, D606.1, F1.1, F1.2, F1.9, J201.3, J202.2, J203.2, J401.2, Q152.2, Q153.2, R104.2, R111.2, R121.2, R123.2, R126.2, R154.2, R156.2, R157.2, R161.2, R163.2, R167.2, R168.2, R170.2, R407.2, R408.2, R409.2, R411.2, R512.2, R514.2, R522.2, R524.2, TP103.1, TP123.1, TP152.1, TP213.1, TP305.1, TP405.1, TP504.1, U101.4, U121.1, U121.9, U151.10, U151.15, U151.16, U151.17, U152.5 (GND), U152.11 (EP), U153.5, U153.11, U201.1, U201.40, U201.41, U202.2, U301.2, U301.8, U301.9, U401.3, U401.8, U401.12, U401.19, U402.1, U402.4, U402.7, U403.2, U404.1, U404.4, U404.7, U501.9, U502.4
GPS_3V3: C402.1, C403.1, C405.1, TP404.1, U401.1, U403.5, U404.8
GPS_5V_IN: C401.1, R401.2, U403.1, U403.3
GPS_ANT_RF_BIASED: L406.1, U401.11
GPS_EXT_ANT: D402.1, J401.1, L406.2
GPS_FIX_RAW: R409.1, U401.5, U404.5
GPS_PPS_BUFFER: R403.1, U402.3
GPS_PPS_MCU: R403.2, U201.9
GPS_PPS_RAW: R408.1, TP403.1, U401.13, U402.5
GPS_RX_BUFFER: R404.1, U404.6
GPS_RX_MODULE: R404.2, TP402.1, U401.10
GPS_SEARCH_BUFFER: R405.1, U404.3
GPS_SEARCH_LED_A: D401.2, R405.2
GPS_TX_BUFFER: R402.1, U402.6
GPS_TX_MCU: R410.2, R411.1, U201.10, U404.2
GPS_TX_MODULE_BUFFERED: R402.2, U201.11
GPS_TX_RAW: R407.1, TP401.1, U401.9, U402.2
INPUT_FAULT_N: R108.2, TP104.1, U101.6
INPUT_GATE: D104.1, Q101.1, R106.2
INPUT_GATE_DRIVE: R106.1, R107.1, U101.8
INPUT_GATE_SLEW: C102.1, R107.2
INPUT_OV: R103.2, R104.1, U101.3
INPUT_SHDN: R105.2, U101.5
INPUT_UV: R102.2, R103.1, U101.2
LED_BLE: R602.1, U201.6
LED_BLE_A: D602.2, R602.2
LED_CAN: R603.1, U201.7
LED_CAN_A: D603.2, R603.2
LED_GPS: R604.1, U201.12
LED_GPS_A: D604.2, R604.2
LED_OIL: R606.1, U201.17
LED_OIL_A: D606.2, R606.2
LED_PWR: R601.1, U201.8
LED_PWR_A: D601.2, R601.2
LED_SYS: R605.1, U201.18
LED_SYS_A: D605.2, R605.2
OIL_5V: C503.1, D501.2, F1.8, R507.2, R521.1, TP505.1
OIL_AMP_OUT: C514.1, R515.1, U502.1
OIL_DVDT: C501.1, U501.12
OIL_EFUSE_OUT: C504.1, C505.1, C506.1, C532.1, D502.1, R507.1, TP510.1, U501.15, U501.16
OIL_EFUSE_RTN: C501.2, R502.2, R504.2, R505.2, TP509.1, U501.8, U501.17
OIL_EXCITATION_ADC: C523.1, D521.2, D522.1, R523.1, R525.2, TP506.1, U201.38
OIL_EXC_AMP_OUT: C524.1, R525.1, U502.7
OIL_EXC_FB: C524.2, R523.2, R524.1, U502.6
OIL_EXC_FILTERED: C521.1, C522.1, R521.2, R522.1, U502.5
OIL_FB: C514.2, R513.2, R514.1, U502.2
OIL_FILTERED: C511.1, C512.1, R511.2, R512.1, TP502.1, U502.3
OIL_ILIM: R505.1, U501.11
OIL_OVP: R503.2, R504.1, U501.5
OIL_POWER_FAULT_N: R506.2, TP508.1, U501.14
OIL_SHDN: TP507.1, U501.7
OIL_SIG: D501.1, F1.7, R511.1, TP501.1
OIL_UVLO: R501.2, R502.1, U501.3
PROTECTED_12V: C103.1, D103.1, D104.2, Q101.3, R109.1, R111.1, TP102.1, U101.7
PROTECT_CTRL_VIN: C101.1, D102.1, R101.2, R105.1, U101.1
RAW_12V: F1.3, F101.1, TP101.1
REV_BLOCKED_12V: D101.1, D105.1, Q101.2, R101.1, R102.1
SUP_RESET_DELAY: R204.2, U202.4
SUP_RESET_RAW: R203.1, U202.1
UART0_RX: J201.4, TP212.1, U201.36
UART0_TX: J201.5, TP211.1, U201.37

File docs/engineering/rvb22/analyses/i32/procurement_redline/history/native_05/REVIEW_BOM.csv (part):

"Reference","Value","Footprint","Manufacturer","MPN","LCSC","Quantity"
"C101","100n /100V X7R","RevB:C_0805_2012Metric","TDK","CGA4J2X7R2A104K125AA","C342919","1"
"C102","10n /100V X7R","RevB:C_0603_1608Metric","TDK","CGA3E2X7R2A103K080AE","C3858696","1"
"C103","2.2u /100V X7R","RevB:C_1210_3225Metric","TDK","CGA6N3X7R2A225K230AB","C342652","1"
"C121","2.2u /100V X7R","RevB:C_1210_3225Metric","TDK","CGA6N3X7R2A225K230AB","C342652","1"
"C122","2.2u /100V X7R","RevB:C_1210_3225Metric","TDK","CGA6N3X7R2A225K230AB","C342652","1"
"C123","100n /100V X7R","RevB:C_0805_2012Metric","TDK","CGA4J2X7R2A104K125AA","C342919","1"
"C124","2.2n /50V C0G 5%","RevB:C_0603_1608Metric","TDK","CGA3E2C0G1H222J080AA","C2169200","1"
"C125","3.3n /100V C0G 5%","RevB:C_0603_1608Metric","TDK","CGA3E2C0G2A332J080AA","C2171993","1"
"C126","100p /50V C0G","RevB:C_0603_1608Metric","TDK","CGA3E2C0G1H101J080AA","C76709","1"
"C127","22u /25V X7R 10%","RevB:C_1210_3225Metric","Taiyo Yuden","MCAST32MSB7226KPNA01","C5372271","1"
"C128","22u /25V X7R 10%","RevB:C_1210_3225Metric","Taiyo Yuden","MCAST32MSB7226KPNA01","C5372271","1"
"C129","2.2u /100V X7R","RevB:C_1210_3225Metric","TDK","CGA6N3X7R2A225K230AB","C342652","1"
"C151","22u /25V X7R 10%","RevB:C_1210_3225Metric","Taiyo Yuden","MCAST32MSB7226KPNA01","C5372271","1"
"C152","220n /50V X7R 10%","RevB:I32_PROCUREMENT_C152","TDK","CGA3E3X7R1H224KT0Y0N","C342967","1"
"C153","1u /16V X7R","RevB:C_0603_1608Metric","Murata","GCM188R71C105KA64D","C161212","1"
"C154","220n /50V X7R 10%","RevB:I32_PROCUREMENT_C154","TDK","CGA3E3X7R1H224KT0Y0N","C342967","1"
"C155","22u /25V X7R 10%","RevB:C_1210_3225Metric","Taiyo Yuden","MCAST32MSB7226KPNA01","C5372271","1"
"C156","22u /25V X7R 10%","RevB:C_1210_3225Metric","Taiyo Yuden","MCAST32MSB7226KPNA01","C5372271","1"
"C157","22u /25V X7R 10%","RevB:C_1210_3225Metric","Taiyo Yuden","MCAST32MSB7226KPNA01","C5372271","1"
"C158","100n /50V X7R","RevB:C_0603_1608Metric","Murata","GCM188R71H104KA57D","C85864","1"
"C159","33n /100V C0G 5% CT","RevB:I32_FINISHED_C159","TDK","CGA4J1C0G2A333J125AE","","1"
"C161","100n /50V X7R ISO INPUT","RevB:I32_FINISHED_C161","Murata","GCM188R71H104KA57D","","1"
"C162","470u /10V POLYMER INPUT","RevB:I32_FINISHED_C162","KEMET","T598X477M010ATE025","","1"
"C165","220n /50V X7R 10% EN DELAY","RevB:I32_PROCUREMENT_C165","TDK","CGA3E3X7R1H224KT0Y0N","C342967","1"
"C166","68n /100V C0G 5% BULK CT","RevB:I32_FINISHED_C166","TDK","CGA5L1C0G2A683J160AE","","1"
"C167","1u /16V X7R BULK INPUT","RevB:I32_FINISHED_C167","Murata","GCM188R71C105KA64D","","1"
"C201","22u /25V X7R 10%","RevB:C_1210_3225Metric","Taiyo Yuden","MCAST32MSB7226KPNA01","C5372271","1"
"C202","100n /50V X7R","RevB:C_0603_1608Metric","Murata","GCM188R71H104KA57D","C85864","1"
"C204","22u /25V X7R 10%","RevB:C_1210_3225Metric","Taiyo Yuden","MCAST32MSB7226KPNA01","C5372271","1"
"C205","100n /50V X7R","RevB:C_0603_1608Metric_RVB22_C205","Murata","GCM188R71H104KA57D","C85864","1"
"C206","680u /6.3V POLYMER","RevB:KEMET_T598_X_7343_Median_RVB22_C206","KEMET","T598X687M006ATE025","","1"
"C301","100n /50V X7R","RevB:C_0603_1608Metric","Murata","GCM188R71H104KA57D","C85864","1"
"C302","1u /16V X7R","RevB:C_0603_1608Metric","Murata","GCM188R71C105KA64D","C161212","1"
"C401","22u /25V X7R 10%","RevB:C_1210_3225Metric","Taiyo Yuden","MCAST32MSB7226KPNA01","C5372271","1"
"C402","22u /25V X7R 10%","RevB:C_1210_3225Metric","Taiyo Yuden","MCAST32MSB7226KPNA01","C5372271","1"
"C403","100n /50V X7R","RevB:C_0603_1608Metric","Murata","GCM188R71H104KA57D","C85864","1"
"C404","100n /50V X7R","RevB:C_0603_1608Metric","Murata","GCM188R71H104KA57D","C85864","1"
"C405","100n /50V X7R","RevB:C_0603_1608Metric","Murata","GCM188R71H104KA57D","C85864","1"
"C501","22n /50V X7R","RevB:C_0603_1608Metric","TDK","CGA3E2X7R1H223K080AE","C2176922","1"
"C502","100n /50V X7R","RevB:C_0603_1608Metric","Murata","GCM188R71H104KA57D","C85864","1"
"C503","100n /100V X7R","RevB:C_0805_2012Metric","TDK","CGA4J2X7R2A104K125AA","C342919","1"
"C504","10u /50V X7R","RevB:KEMET_C1210_10u50V","KEMET","C1210C106K5RACTU","C2167688","1"
"C505","10u /50V X7R","RevB:KEMET_C1210_10u50V","KEMET","C1210C106K5RACTU","C2167688","1"
"C506","10u /50V X7R","RevB:KEMET_C1210_10u50V","KEMET","C1210C106K5RACTU","C2167688","1"
"C511","1u /16V X7R","RevB:C_0603_1608Metric","Murata","GCM188R71C105KA64D","C161212","1"
"C512","1u /16V X7R","RevB:C_0603_1608Metric","Murata","GCM188R71C105KA64D","C161212","1"
"C513","22n /50V X7R","RevB:C_0603_1608Metric","TDK","CGA3E2X7R1H223K080AE","C2176922","1"
"C514","100p /50V C0G5%","RevB:C_0603_1608Metric","TDK","CGA3E2C0G1H101J080AA","C76709","1"
"C521","1u /16V X7R","RevB:C_0603_1608Metric","Murata","GCM188R71C105KA64D","C161212","1"
"C522","1u /16V X7R","RevB:C_0603_1608Metric","Murata","GCM188R71C105KA64D","C161212","1"
"C523","22n /50V X7R","RevB:C_0603_1608Metric","TDK","CGA3E2X7R1H223K080AE","C2176922","1"
"C524","100p /50V C0G5%","RevB:C_0603_1608Metric","TDK","CGA3E2C0G1H101J080AA","C76709","1"
"C531","100n /50V X7R","RevB:C_0603_1608Metric","Murata","GCM188R71H104KA57D","C85864","1"
"C532","10n /50V C0G 5% OUT HF","RevB:C_0603_1608Metric","Murata","GRM1885C1H103JA01D","","1"
"D101","S5J /600V REVERSE BLOCK","RevB:D_SMC","Vishay","S5JHE3_A/H","","1"
"D102","SMAJ30A /TVS","RevB:D_SMA","Vishay","SMAJ30AHE3_A/H","C1978408","1"
"D103","SMCJ24A /TVS","RevB:D_SMC_RVB22_D103","Vishay","SMCJ24AHE3_A/H","C1981952","1"
"D104","15V GATE CLAMP","RevB:D_SOD-123F","Nexperia","BZT52H-B15-QX","C7507926","1"
"D105","SMCJ110A /RAW OV CLAMP","RevB:D_SMC","Vishay","SMCJ110AHE3_A/H","","1"
"D301","ESD2CAN24DBZRQ1","RevB:SOT-23","Texas Instruments","ESD2CAN24DBZRQ1","C5736151","1"
"D401","SEARCH (blink / no fix)","RevB:LED_0603_1608Metric","Kingbright","APT1608SGC","C5875754","1"
"D402","TPD1E05U06DPYR","RevB:TI_DPY0002A_TPD1E05U06_SMDMask","Texas Instruments","TPD1E05U06DPYR","C436349","1"
"D501","ESD2CAN24DBZRQ1","RevB:SOT-23","Texas Instruments","ESD2CAN24DBZRQ1","C5736151","1"
"D502","SS16 /60V Schottky","RevB:D_SMA","Vishay","SS16HE3_B/H","C266798","1"
"D511","PMEG2010BEA,115","RevB:Nexperia_SOD323_PMEG2010BEA","Nexperia","PMEG2010BEA,115","C455041","1"
"D512","PMEG2010BEA,115","RevB:Nexperia_SOD323_PMEG2010BEA","Nexperia","PMEG2010BEA,115","C455041","1"
"D521","PMEG2010BEA,115","RevB:Nexperia_SOD323_PMEG2010BEA","Nexperia","PMEG2010BEA,115","C455041","1"
"D522","PMEG2010BEA,115","RevB:Nexperia_SOD323_PMEG2010BEA","Nexperia","PMEG2010BEA,115","C455041","1"
"D601","PWR","RevB:LED_0603_1608Metric","Kingbright","APT1608SGC","C5875754","1"
"D602","BLE","RevB:LED_0603_1608Metric","Kingbright","APT1608SGC","C5875754","1"
"D603","CAN","RevB:LED_0603_1608Metric","Kingbright","APT1608SGC","C5875754","1"
"D604","GPS","RevB:LED_0603_1608Metric","Kingbright","APT1608SGC","C5875754","1"
"D605","SYS","RevB:LED_0603_1608Metric","Kingbright","APT1608SGC","C5875754","1"
"D606","OIL","RevB:LED_0603_1608Metric","Kingbright","APT1608SGC","C5875754","1"
"F1","0430451200 / TIN NEW HARNESS","RevB:Molex_Micro-Fit_3.0_43045-1200_2x06_P3.00mm_Horizontal_RVB22_F1","Molex","0430451200","C277636","1"
"F101","1A /500VDC","RevB:Fuse_Littelfuse-NANO2-885","Littelfuse","0885001.DR","C2879865","1"
"J202","RESET — short to reset","RevB:Wurth_61300211121_1x02","Wurth Elektronik","61300211121","C2915055","1"
"J203","BOOT — hold low on reset","RevB:Wurth_61300211121_1x02","Wurth Elektronik","61300211121","C2915055","1"
"J401","U.FL-R-SMT-1(80)","RevB:Hirose_UFL_R_SMT_1_80_RevB","Hirose","U.FL-R-SMT-1(80)","C88374","1"
"L121","47u /100mOhm 2.5A BPCI","RevB:I32_PROCUREMENT_L121","Chilisin / Pulse","BPCI00121280470M00","C6471075","1"
"L151","15u /XGL5030","RevB:L_Coilcraft_XAL5030-XXX","Coilcraft","XGL5030-153MEC","","1"
"L406","1.6nH 5% RF MATCH","RevB:Murata_LQW18AS_1608","Murata","LQW18AS1N6J0ZD","","1"
"Q101","STD25NF20 /200V","RevB:TO-252-2","STMicroelectronics","STD25NF20","C388326","1"
"Q152","DMG2302UKQ /DISCHARGE","RevB:I32_FINISHED_Q152","Diodes Incorporated","DMG2302UKQ-7","","1"
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
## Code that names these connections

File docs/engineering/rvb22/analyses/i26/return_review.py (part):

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 'GPS_ANT_RF_BIASED','GPS_EXT_ANT','GPS_TX_RAW','GPS_TX_MCU','GPS_TX_BUFFER',
 'GPS_TX_MODULE_BUFFERED','GPS_RX_MODULE','GPS_RX_BUFFER','GPS_PPS_RAW',
 'GPS_PPS_BUFFER','GPS_PPS_MCU','OIL_EXCITATION_ADC','UART0_RX','UART0_TX',
 'ESP_EN','ESP_GPIO0','OIL_FILTERED','OIL_EXC_FILTERED','OIL_SIG','OIL_FB',
 'OIL_EXC_FB','OIL_AMP_OUT','OIL_EXC_AMP_OUT','GPS_FIX_RAW','GPS_SEARCH_BUFFER'}
SOURCE_CLASSES = {
 'CAN_TX_MCU':'GPIO5 launch; R301 DNP isolates this stub from TXD. No intended release transitions.',
 'CAN_RX_MCU':'U301 RXD through R302 1kohm into GPIO4; receive path.',
 'CAN_RXD':'U301 RXD BEFORE R302 1kohm; do not confuse this with the filtered MCU-side net.',
 'CAN_TXD':'U301 TXD held recessive by fitted R303 10kohm; R301 DNP; no intentional TX.',
 'GPS_TX_RAW':'PA1616D TX0 into U402 LVC input; raw UART source edge not specified.',
 'GPS_PPS_RAW':'PA1616D PPS into U402 LVC input; PPS repetition frequency is not edge rate.',
 'GPS_TX_BUFFER':'U402 LVC output BEFORE R402 220ohm.',
 'GPS_PPS_BUFFER':'U402 LVC output BEFORE R403 220ohm.',
 'GPS_TX_MODULE_BUFFERED':'U402 via R402 220ohm to GPIO18; active GPS receive path.',
 'GPS_TX_MCU':'GPIO17 output into U404 input; active GPS command path.',
 'GPS_RX_BUFFER':'U404 LVC output BEFORE R404 220ohm.',
 'GPS_RX_MODULE':'U404 via R404 220ohm to PA1616D RX0.',
 'GPS_PPS_MCU':'U402 via R403 220ohm to GPIO16.',
 'GPS_SEARCH_BUFFER':'U404 LVC output drives R405 1kohm and D401; indicator, not timing input.',
 'ESP_EN':'Supervisor/reset/pullup network; reset immunity must be assessed separately from UART.',
 'ESP_GPIO0':'Boot strap/programming fixture network; not a high-rate data interface.'}

def require(value, message):
    if not value:
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      'finding_counts':dict(collections.Counter(r['net'] for r in findings)),'findings':findings,'signal_via_count':len(transfers),'signal_vias':transfers,
      'limitations':['Reference polygons and signal centerlines are nominal; no universal etched neck-width or RF-current-distribution proof.',
      'Own signal antipads are explicitly excluded, not credited as ground copper.',
      'CAN_RXD before R302, buffered GPS receive into GPIO18, EN, GPIO0 and indicator/control applicability now appear explicitly.',
      'A nearby through-ground-via is not accepted without a real copper path to both return planes.',
      'The I26 native geometry reference predates I28; I28 changes only U121 fitted metadata, while exact current-source native ERC/DRC/manufacturing verification is performed separately.',
      'Existing RF matching, CAN receive-branch and private DC return models retain their separate scopes.'],
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

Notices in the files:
README.md:
License & acknowledgements:
This project builds on the open-source work of the ESP32, NimBLE, and RaceChrono communities. Please review the individual licenses inside `libraries/` before redistributing binaries.
